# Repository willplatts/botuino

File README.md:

# scout-robot
Arduino compatible robot for scouts

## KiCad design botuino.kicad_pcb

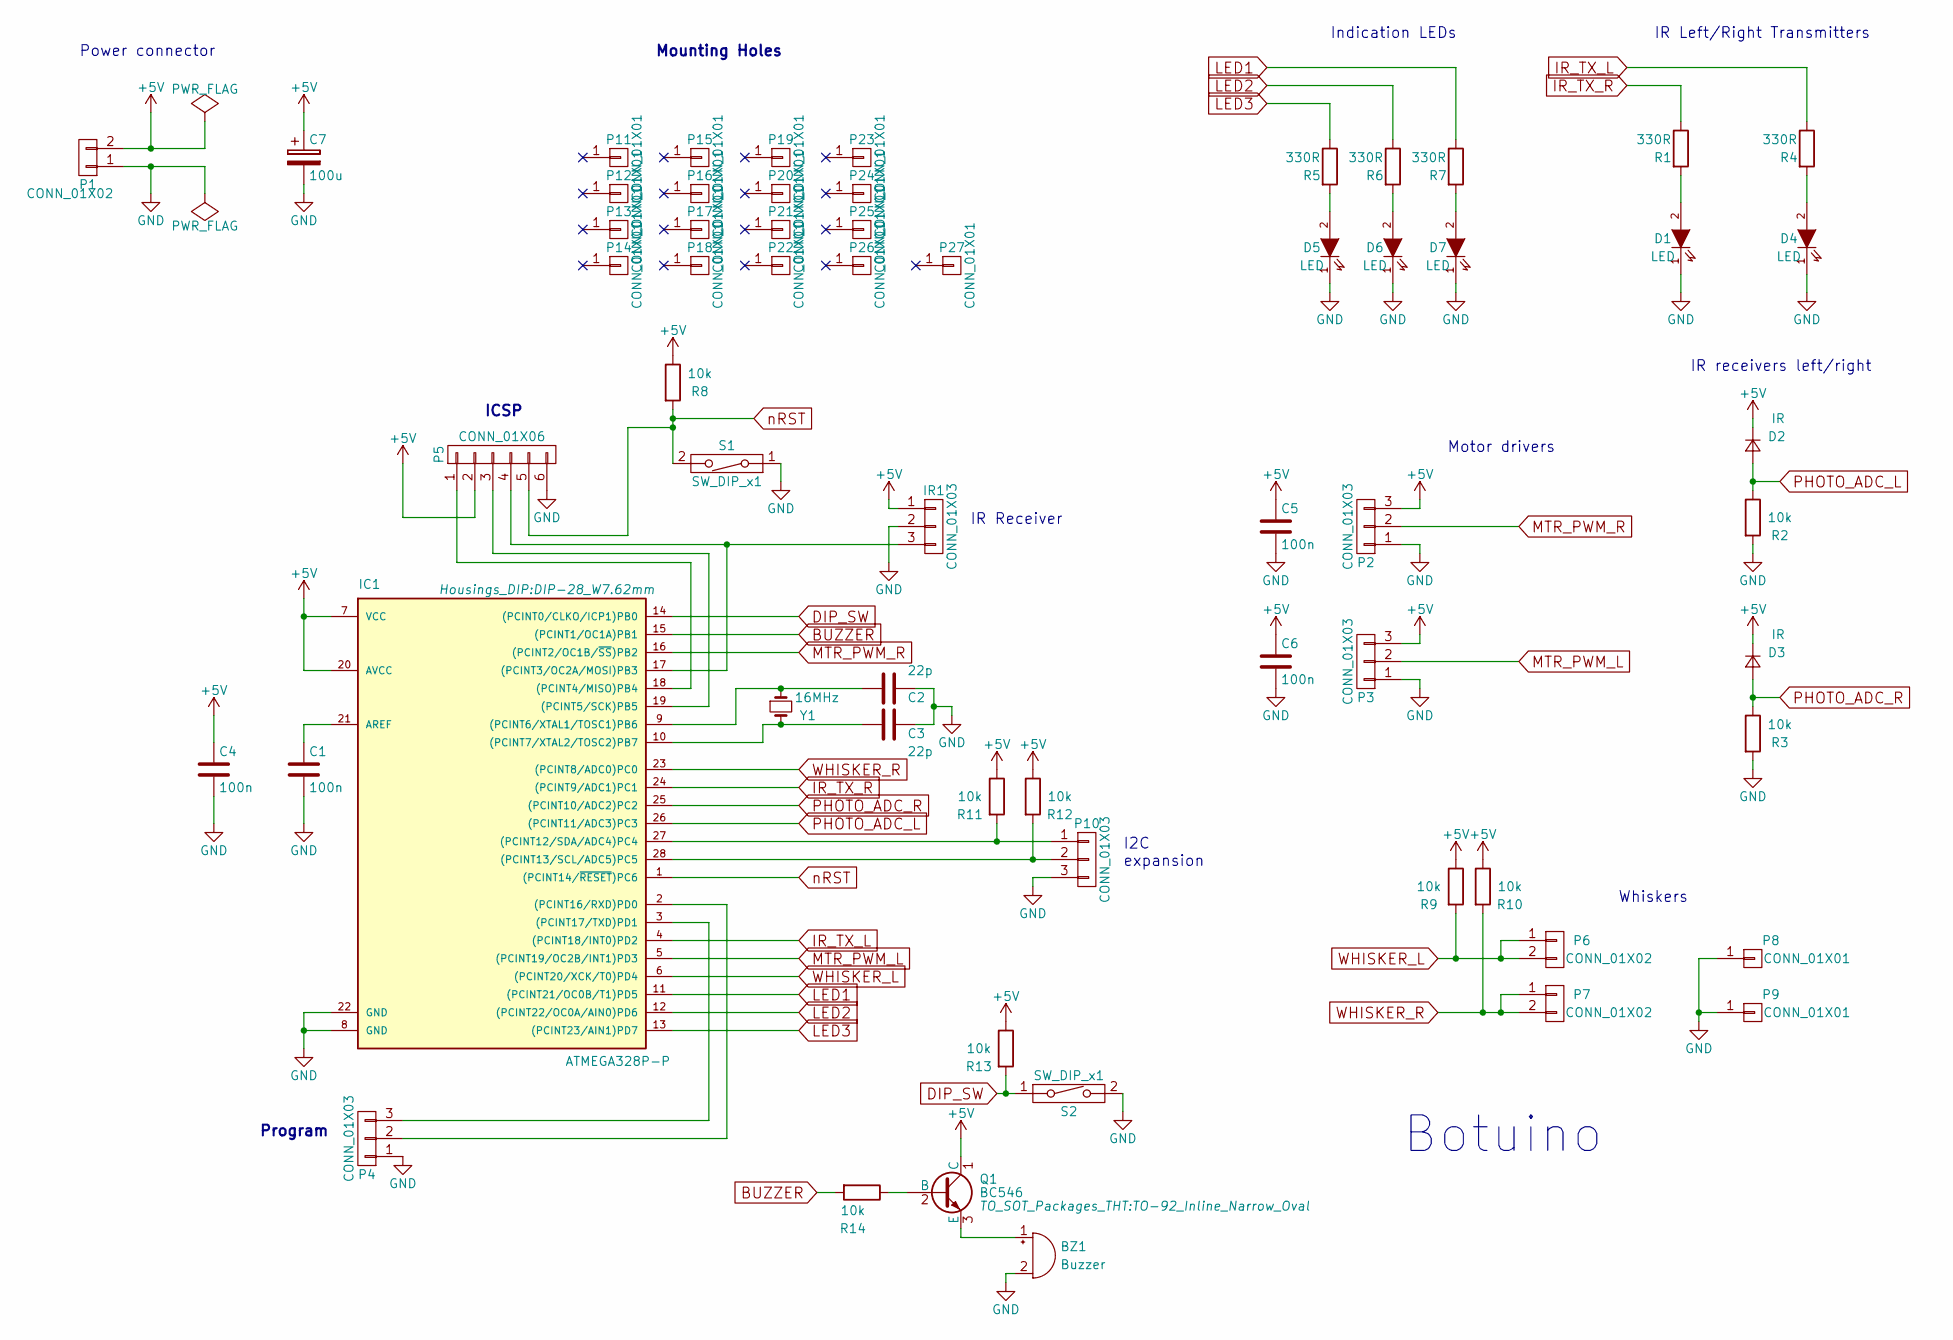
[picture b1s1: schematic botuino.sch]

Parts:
BZ1: Buzzer; Buzzer_12x9.5RM7.6
C1, C4, C5, C6: 100n; C_Disc_D5.1mm_W3.2mm_P5.00mm
C2, C3: 22p; C_Disc_D3.8mm_W2.6mm_P2.50mm
C7: 100u; CP_Radial_D5.0mm_P2.00mm
D1, D4, D5, D6, D7: LED; LED-5MM
D2, D3: IR; LED-5MM
IC1: ATMEGA328P-P; DIP-28_W7.62mm
IR1: CONN_01X03; Pin_Header_Straight_1x03_Pitch2.54mm
P1, P6, P7: CONN_01X02; Pin_Header_Straight_2x01_Pitch2.54mm
P2, P3, P4, P10: CONN_01X03; Pin_Header_Straight_1x03_Pitch2.54mm
P5: CONN_01X06; Pin_Header_Straight_1x06_Pitch2.54mm
P8, P9: CONN_01X01; 1pin
P11, P12, P13, P14, P15, P16, P17, P18, P19, P20, P21, P22, P23, P24, P25, P26, P27: CONN_01X01; MountingHole_3.2mm_M3
Q1: BC546; TO-92_Inline_Narrow_Oval
R1, R4, R5, R6, R7: 330R; R_Axial_DIN0207_L6.3mm_D2.5mm_P7.62mm_Horizontal
R2, R3, R8, R9, R10, R11, R12, R13, R14: 10k; R_Axial_DIN0207_L6.3mm_D2.5mm_P7.62mm_Horizontal
S1: SW_DIP_x1; SW_PUSH_6mm
S2: SW_DIP_x1; SW_DIP_x1_W7.62mm_Slide
Y1: 16MHz; Crystal_HC49-U_Vertical

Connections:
+5V: C4.1, C5.1, C6.1, C7.1, D2.1 (K), D3.1 (K), IC1.7 (VCC), IC1.20 (AVCC), IR1.1, P1.2, P2.3, P3.3, P5.2, Q1.1 (C), R8.1, R9.1, R10.1, R11.1, R12.1, R13.1
BUZZER: IC1.15 ((PCINT1/OC1A)PB1), R14.2
DIP_SW: IC1.14 ((PCINT0/CLKO/ICP1)PB0), R13.2, S2.1
GND: BZ1.2 (+), C1.2, C2.1, C3.1, C4.2, C5.2, C6.2, C7.2, D1.1 (K), D4.1 (K), D5.1 (K), D6.1 (K), D7.1 (K), IC1.8 (GND), IC1.22 (GND), IR1.2, P1.1, P2.1, P3.1, P4.1, P5.6, P8.1, P9.1, P10.3, R2.2, R3.2, S1.1, S2.2
IR_TX_L: IC1.4 ((PCINT18/INT0)PD2), R4.1
IR_TX_R: IC1.24 ((PCINT9/ADC1)PC1), R1.1
LED1: IC1.11 ((PCINT21/OC0B/T1)PD5), R7.1
LED2: IC1.12 ((PCINT22/OC0A/AIN0)PD6), R6.1
LED3: IC1.13 ((PCINT23/AIN1)PD7), R5.1
MTR_PWM_L: IC1.5 ((PCINT19/OC2B/INT1)PD3), P3.2
MTR_PWM_R: IC1.16 ((PCINT2/OC1B/~SS~)PB2), P2.2
unnamed: BZ1.1 (-), Q1.3 (E)
unnamed: C1.1, IC1.21 (AREF)
unnamed: C2.2, IC1.9 ((PCINT6/XTAL1/TOSC1)PB6), Y1.1
unnamed: C3.2, IC1.10 ((PCINT7/XTAL2/TOSC2)PB7), Y1.2
unnamed: D1.2 (A), R1.2
unnamed: D4.2 (A), R4.2
unnamed: D5.2 (A), R5.2
unnamed: D6.2 (A), R6.2
unnamed: D7.2 (A), R7.2
unnamed: IC1.2 ((PCINT16/RXD)PD0), P4.2
unnamed: IC1.3 ((PCINT17/TXD)PD1), P4.3
unnamed: IC1.17 ((PCINT3/OC2A/MOSI)PB3), IR1.3, P5.4
unnamed: IC1.18 ((PCINT4/MISO)PB4), P5.1
unnamed: IC1.19 ((PCINT5/SCK)PB5), P5.3
unnamed: IC1.27 ((PCINT12/SDA/ADC4)PC4), P10.1, R11.2
unnamed: IC1.28 ((PCINT13/SCL/ADC5)PC5), P10.2, R12.2
unnamed: Q1.2 (B), R14.1
PHOTO_ADC_L: D2.2 (A), IC1.26 ((PCINT11/ADC3)PC3), R2.1
PHOTO_ADC_R: D3.2 (A), IC1.25 ((PCINT10/ADC2)PC2), R3.1
WHISKER_L: IC1.6 ((PCINT20/XCK/T0)PD4), P6.1, P6.2, R9.2
WHISKER_R: IC1.23 ((PCINT8/ADC0)PC0), P7.1, P7.2, R10.2
nRST: IC1.1 ((PCINT14/~RESET~)PC6), P5.5, R8.2, S1.2

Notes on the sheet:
IR Left/Right Transmitters
Motor drivers
Power connector
IR receivers left/right
Indication LEDs
ICSP
Whiskers
Program
Botuino
IR Receiver
I2C expansion
Mounting Holes

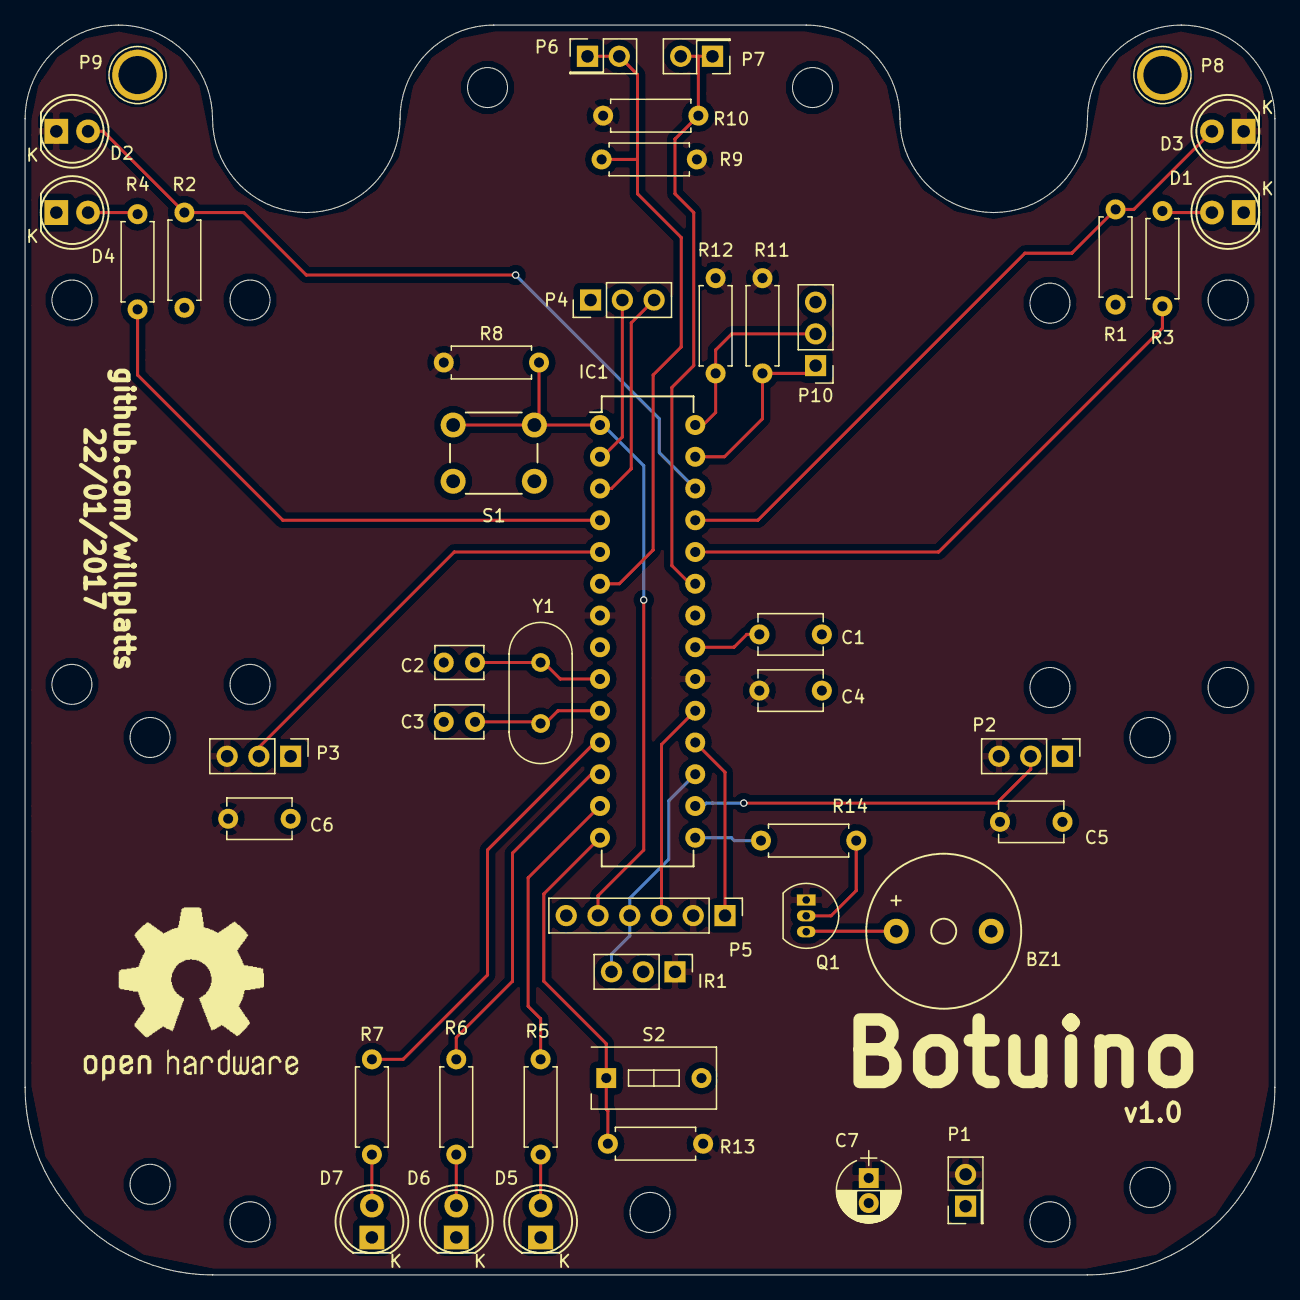
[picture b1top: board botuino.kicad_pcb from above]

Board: 2 copper layers, 100.0 x 100.0 mm, 62 parts (0 on the bottom side), 33 nets.

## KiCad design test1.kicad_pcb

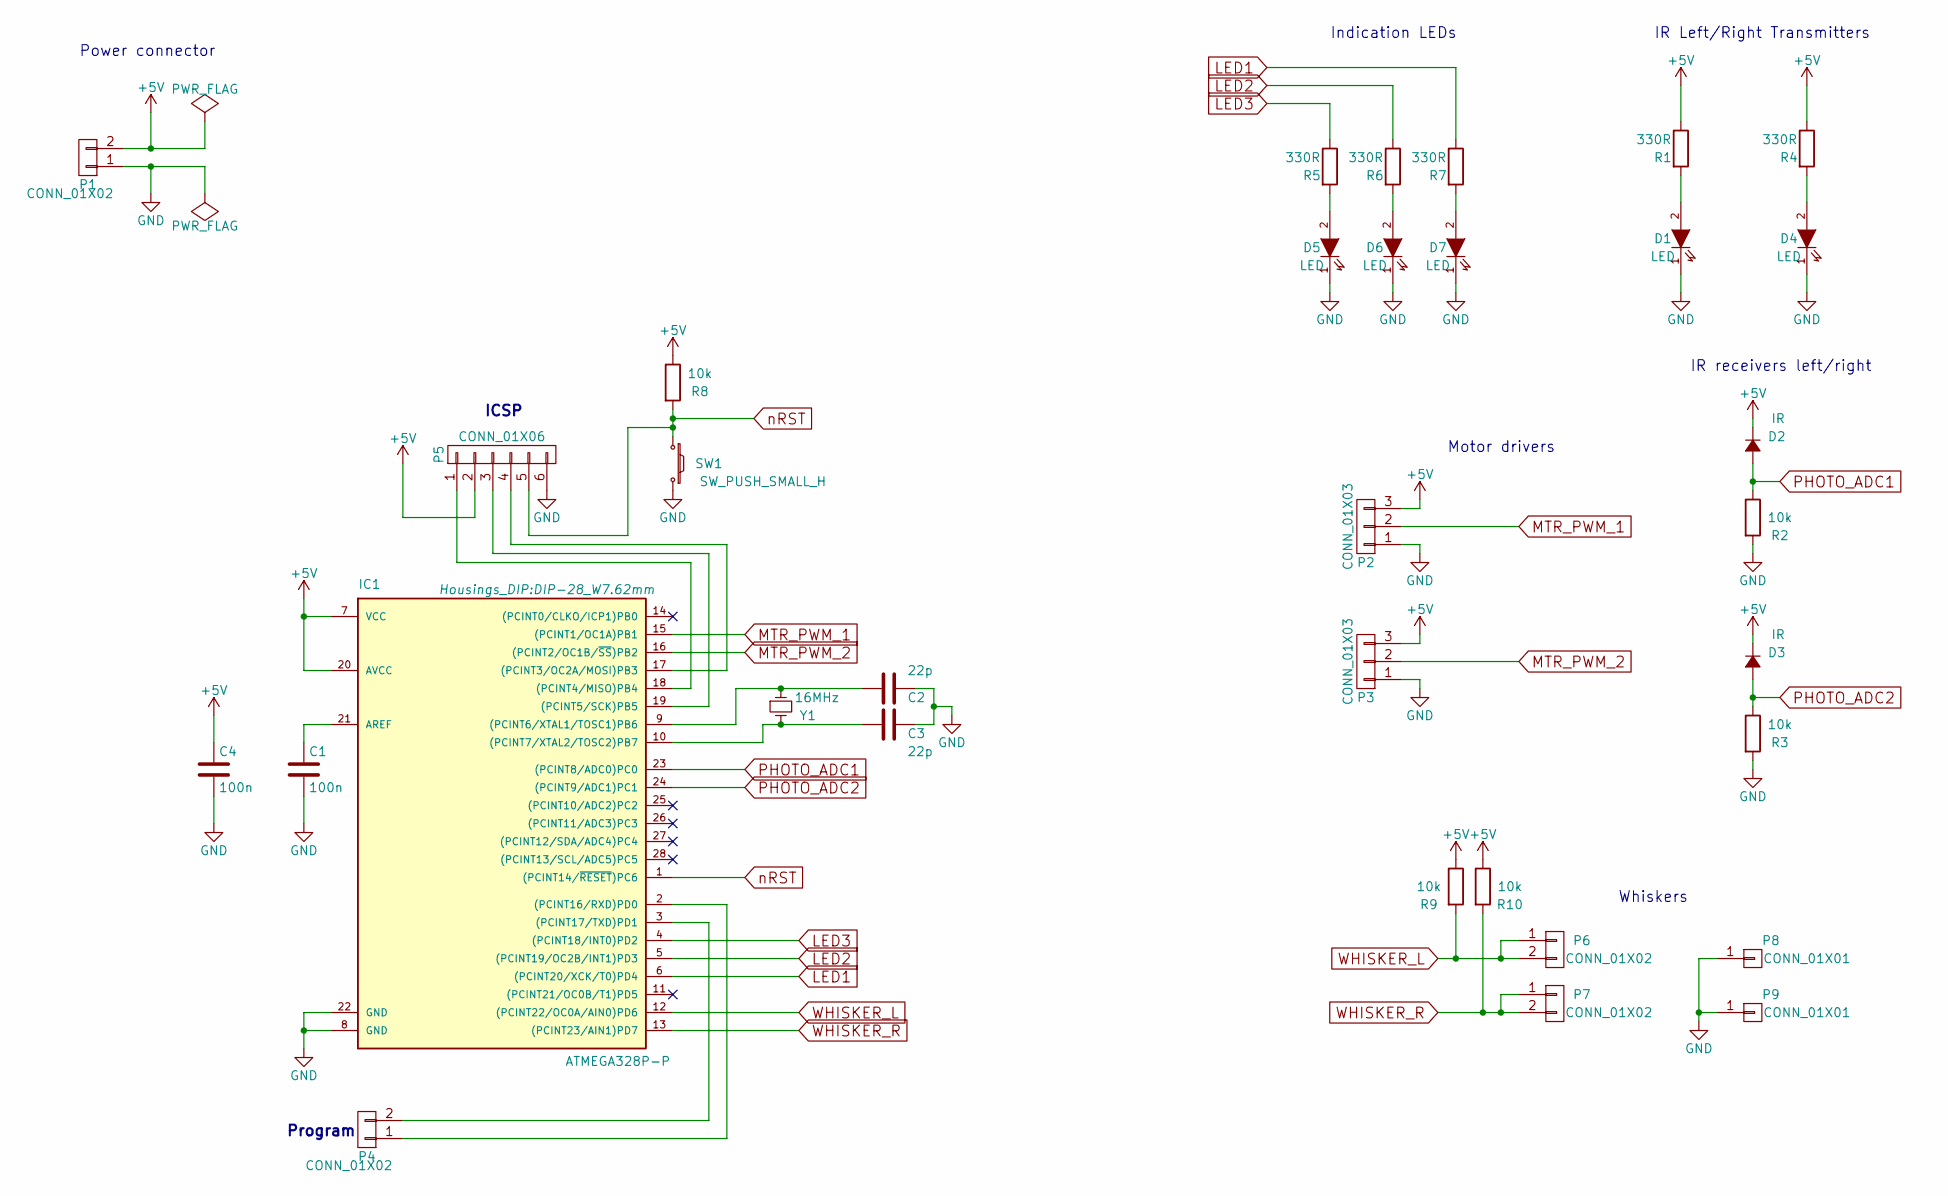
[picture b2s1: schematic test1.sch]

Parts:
C1, C4: 100n; C_Disc_D3_P2.5
C2, C3: 22p; C_Disc_D3_P2.5
D1, D4, D5, D6, D7: LED
D2, D3: IR
IC1: ATMEGA328P-P; DIP-28_W7.62mm
P1, P4: CONN_01X02; Pin_Header_Straight_1x02
P2, P3: CONN_01X03
P5: CONN_01X06
P6, P7: CONN_01X02
P8, P9: CONN_01X01
R1, R4, R5, R6, R7: 330R
R2, R3, R8, R9, R10: 10k
SW1: SW_PUSH_SMALL_H
Y1: 16MHz

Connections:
+5V: C4.1, D2.1 (K), D3.1 (K), IC1.7 (VCC), IC1.20 (AVCC), P1.2, P2.3, P3.3, P5.2, R1.1, R4.1, R8.1, R9.1, R10.1
GND: C1.2, C2.1, C3.1, C4.2, D1.1 (K), D4.1 (K), D5.1 (K), D6.1 (K), D7.1 (K), IC1.8 (GND), IC1.22 (GND), P1.1, P2.1, P3.1, P5.6, P8.1, P9.1, R2.2, R3.2, SW1.2
LED1: IC1.6 ((PCINT20/XCK/T0)PD4), R7.1
LED2: IC1.5 ((PCINT19/OC2B/INT1)PD3), R6.1
LED3: IC1.4 ((PCINT18/INT0)PD2), R5.1
MTR_PWM_1: IC1.15 ((PCINT1/OC1A)PB1), P2.2
MTR_PWM_2: IC1.16 ((PCINT2/OC1B/~SS~)PB2), P3.2
unnamed: C1.1, IC1.21 (AREF)
unnamed: C2.2, IC1.9 ((PCINT6/XTAL1/TOSC1)PB6), Y1.1
unnamed: C3.2, IC1.10 ((PCINT7/XTAL2/TOSC2)PB7), Y1.2
unnamed: D1.2 (A), R1.2
unnamed: D4.2 (A), R4.2
unnamed: D5.2 (A), R5.2
unnamed: D6.2 (A), R6.2
unnamed: D7.2 (A), R7.2
unnamed: IC1.2 ((PCINT16/RXD)PD0), P4.1
unnamed: IC1.3 ((PCINT17/TXD)PD1), P4.2
unnamed: IC1.17 ((PCINT3/OC2A/MOSI)PB3), P5.4
unnamed: IC1.18 ((PCINT4/MISO)PB4), P5.1
unnamed: IC1.19 ((PCINT5/SCK)PB5), P5.3
PHOTO_ADC1: D2.2 (A), IC1.23 ((PCINT8/ADC0)PC0), R2.1
PHOTO_ADC2: D3.2 (A), IC1.24 ((PCINT9/ADC1)PC1), R3.1
WHISKER_L: IC1.12 ((PCINT22/OC0A/AIN0)PD6), P6.1, P6.2, R9.2
WHISKER_R: IC1.13 ((PCINT23/AIN1)PD7), P7.1, P7.2, R10.2
nRST: IC1.1 ((PCINT14/~RESET~)PC6), P5.5, R8.2, SW1.1

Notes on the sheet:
IR Left/Right Transmitters
Motor drivers
Power connector
IR receivers left/right
Indication LEDs
ICSP
Whiskers
Program

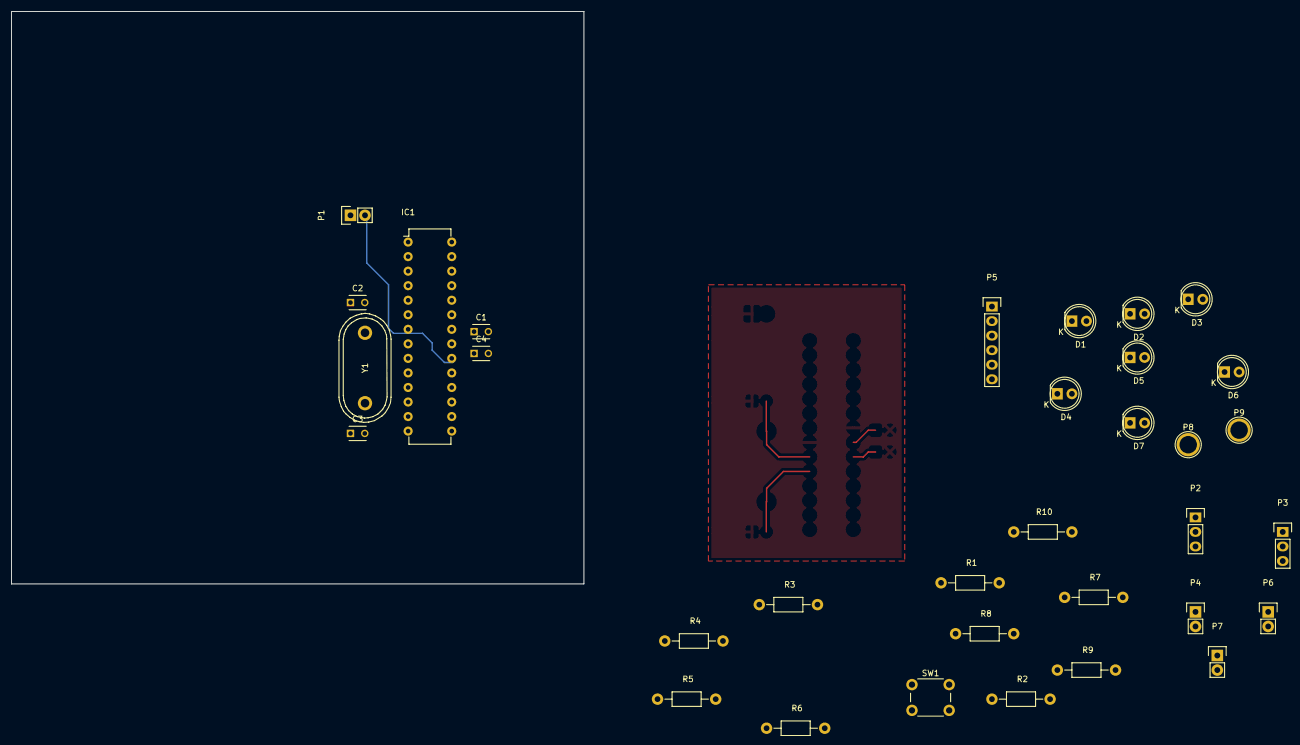
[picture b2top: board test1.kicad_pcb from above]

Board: 2 copper layers, 100.0 x 100.0 mm, 33 parts (0 on the bottom side), 25 nets.

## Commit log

2016-10-12 Adding initial KiCad files for scout robot
2016-10-17 Adding some extra components
2017-01-04 Changes to schematic and PCB
2017-01-26 Multiple changes to project. Changing name to "Botuino". Up to version 1.0
2017-01-26 Updating schematic with title and version number
